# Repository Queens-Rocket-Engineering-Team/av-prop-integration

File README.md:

# Propulsion Integration Systems
> 2025-2026 Season - Propulsion Integration Projects

- Repository contains Avionics schematics, PCBs, and firmware for integrating with the propulsion stack.

### Folder Structure
- [`/Schematics`](./Schematics/) : Electrical design files (KiCad V8)  
- [`/Firmware`](./Firmware/) : C/C++ Code
- [`/Datasheets`](./Datasheets/) : Datasheets and reference materials  

### Documentation
- Boards and code are documented through `README` files in their respective directories. 

### Usage 
- To add or update features and work on new projects, create a new branch. 
- For **PCB** projects, name the branch with the convention: `pcb/board-name` or `pcb/board-feature` for updates.
- For **firmware** projects, name the branch with the convention: `fw/project-name` or `fw/project-feature` for updates.

--- 

QRET Avionics 25/26

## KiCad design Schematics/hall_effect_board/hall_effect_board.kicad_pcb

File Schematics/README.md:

# Propulsion Integration Schematics
This directory contains all schematics involved in this iteration of the Avionics Propulsion Integration system.
- All schematic and board files are created with **Kicad V8**.

Including: 

### Lower Control Board (Hydra)
- Launch control board for the **lower** valve bay. 
- Features valve control, analog sensing, and communication via CAN. 
- Interfaces with an STM32F103x8 microcontroller, controls two solenoids, reads from one Thermocouple, two Pressure Transducers, and two Hall-Effect sensors.

### Upper Control Board (Pegasus)
- Launch control board for the **upper** valve bay. 
- Features valve control, analog sensing, and communication via CAN **and** WIFI. 
- Interfaces with an ESP32-S3 microcontroller, controls two solenoids, reads two Pressure Transducers, and one Hall-Effect sensor.

### Hall Effect Breakout Board 
- Breakout board for a TMAG5273 Hall-Effect Sensor.
- Supports communication via I2C. 

### Shared Circuit Modules
- Circuitry used across both control boards.
- Solenoid control, pressure transducer and thermocouple entry circuitry. 

Usage:
> To create a new board
1. Launch KiCad v8. 
2. Navigate to the **File** menu and select **New Project...** or use the command `Ctrl+N`. 
3. This will open the file explorer. Ensure you are in the `/Schematics` directory. 
4. Name the new board descriptively -- this is also the name of the KiCad project.
    - A **descriptive** name clearly states its function or category. 
    - A name that follows the theme of the rocket should be kept on the board or in schematic files -- not as the name of the KiCad Project. (i.e. "Hydra" for the lower launch control board is a theme-following name)
    - Descriptive shorthands like `lc` (Launch Control) can be helpful in naming boards/projects.
5. Before creating the project, ensure the *Create a new folder for project* box is selected in the bottom-right section of the file explorer. 
6. Press "Save" to create a new project. 
7. In the folder created by KiCad, it wil be helpful to create folders for component symbols, footprints, and models. 
   - You're all done -- it's also always smart to look at existing projects for additional guidance.
  
> To add symbols, footprints, and models
1. Download and unzip resources from a provider like [SnapMagic](https://www.snapeda.com/home/) , [UltraLibrarian](https://www.ultralibrarian.com/), etc.
2. Move your downloaded resources.
    - For **symbols** move the raw `kicad_sym` file into your `symbols` folder.
    - For **footprints** move the `kicad_mod` file that is **in** an appropiately named folder into your `footprints` folder.
    - For **models** move the raw `STEP` file into your `models` folder.
3. To import resources navigate to the **Preferences** menu and select **Manage Symbol Libraries** -- note that this wil be **Manage Footprint Libraries** if you are in the PCB editor.
4. Switch the tab to **Project-Specific Libraries** and from there select the insert & folder icon to add your resource via the file explorer. 
5. After adding your resource select save and you're good to select it in the editor. 
   
6. For importing **3D-models**, navigate to the associated footprint in the PCB editor. 
7. Select it and press `E` to open the properties menu. 
8. Navigate to the **3D Models** tab to add your model through the file explorer. 
9. Press save. `Ctrl+S`

--- 

QRET Avionics 25/26

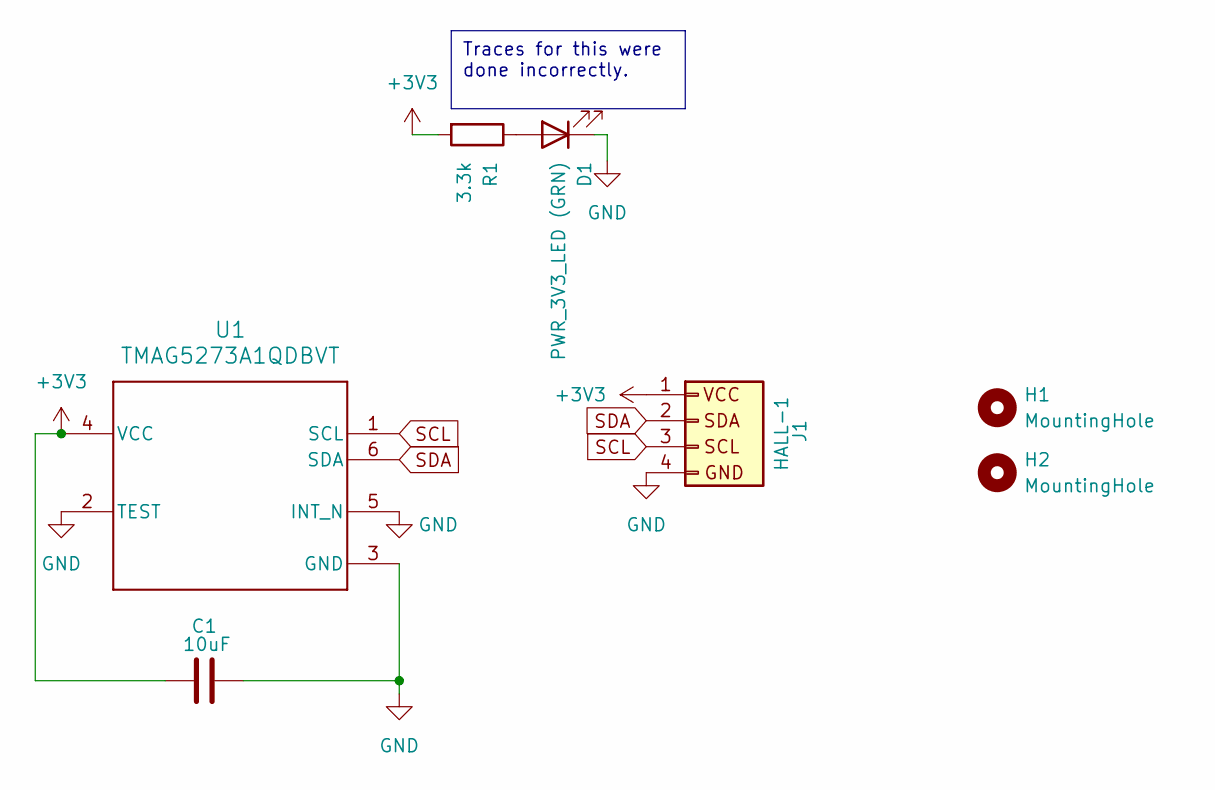
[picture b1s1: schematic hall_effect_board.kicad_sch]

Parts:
C1: 10uF; C_0805_2012Metric_Pad1.18x1.45mm_HandSolder; JLCSC C15850
D1: PWR_3V3_LED (GRN); LED_0603_1608Metric; JLCSC C2297
H1, H2: MountingHole; MountingHole_3.2mm_M3_ISO14580_Pad
J1: HALL-1; Molex_Nano-Fit_105313-xx04_1x04_P2.50mm_Horizontal; Digikey 455-S04B-PASK-2-ND
R1: 3.3k; R_0603_1608Metric; JLCSC C22978
U1: TMAG5273A1QDBVT; DBV0006A-IPC_A; Digikey 296-TMAG5273A1QDBVTCT-ND

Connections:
+3V3: C1.1, J1.1, R1.2, U1.4 (VCC)
GND: C1.2, D1.1 (K), J1.4, U1.2 (TEST), U1.3 (GND), U1.5 (INT_N)
unnamed: D1.2 (A), R1.1
SCL: J1.3, U1.1 (SCL)
SDA: J1.2, U1.6 (SDA)

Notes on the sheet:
Traces for this were done incorrectly.

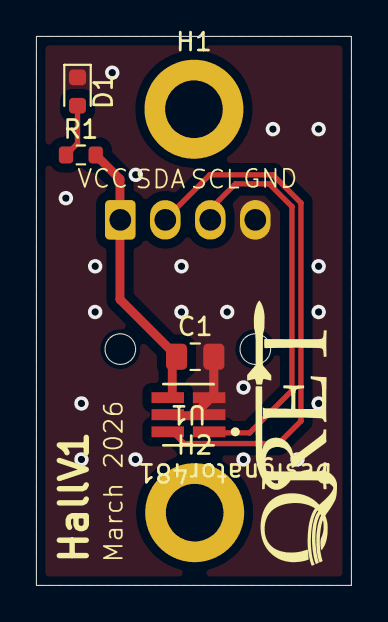
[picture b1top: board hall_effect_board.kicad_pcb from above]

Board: 2 copper layers, 17.5 x 30.5 mm, 7 parts (1 on the bottom side), 5 nets.

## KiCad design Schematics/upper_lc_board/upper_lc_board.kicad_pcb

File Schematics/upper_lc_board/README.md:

# Upper Control Board (PEGASUS) Documentation

<!--- removed left align div - weird github web issue --->
<details>
<summary><strong>Table of Contents</strong></summary>

- [Upper Control Board (PEGASUS) Documentation](#upper-control-board-pegasus-documentation)
  - [Overview](#overview)
    - [Key Features](#key-features)
  - [Circuit Design](#circuit-design)
    - [Power Management](#power-management)
      - [Power Entry](#power-entry)
      - [Power MUX](#power-mux)
      - [Power Switching](#power-switching)
    - [MCU Breakout](#mcu-breakout)
      - [Mode Selection](#mode-selection)
      - [CANBUS Interface](#canbus-interface)
      - [USB Interface](#usb-interface)
      - [System Feedback](#system-feedback)
    - [Valve Control](#valve-control)
    - [Sensing](#sensing)
      - [Data Acquisition](#data-acquisition)
      - [Pressure Transducers](#pressure-transducers)
  - [Board Design](#board-design)
    - [Physical Design Notes](#physical-design-notes)
    - [Electrical Characteristics](#electrical-characteristics)
    - [System Partitioning](#system-partitioning)
  - [Revision History](#revision-history)
  - [Contributors](#contributors)

</details>

---

## Overview

<em>Fig. 1: Pegasus</em>

The **Upper LC/Pegasus** board is a control board designed for integration with the rocket's propulsion system.
It operates in the **upper valve bay**, and drives a solenoid to control the rocket's vent valve.
This board supports analog pressure sensing, a digital hall-effect sensor for solenoid-status reading, and communication with the rest of the stack through CANbus. It is also **WiFi-capable**.

Interfaces with:
- ESP32-S3 Module
- Two 24V 205292 Solenoids
- Two 24V 4-20mA Pressure Transducers (PT)
- One TMAG273 digital hall-effect sensor (via breakout board)

### Key Features

- ESP32-S3 microcontroller with integrated WiFi
- I2C and SPI interfaces for sensor integration
- Controlled power delivery for sensors
- ORing circuits for power management
- Auditory and visual indication for status and debugging
- 4-layer PCB with dedicated ground planes
- Protection and filtering components across board

---

## Circuit Design

---

### Power Management

This board receives power from the Hybrid Power Module through the Backplane.
For more information on power delivery, check out [this repository](https://github.com/Queens-Rocket-Engineering-Team/av-power).

The supply delivers **three** levels of voltage to the board:

| Voltage (V) | Purpose |
|-------------|---------|
| 3.3 | Logic supply for microcontroller and other peripheral devices; also serves as a reference for signal conditioning and protection circuits |
| 5 | Intermediate supply for specific peripheral devices |
| 24 | High-voltage supply for driving external devices such as solenoids and sensors |

> **Note:** 3.3V is referred to as **3V3** throughout this document.

#### Power Entry

Power rails enter through a PCIe connector (Stack Edge Connector) and are conditioned by bulk filtering and input protection circuitry. These circuits apply to the 5V and 24V rails, each decoupled with 100 µF electrolytic capacitors to handle voltage transients and provide local energy storage. The 24V rail includes a 2A fuse for overcurrent protection.

Other power sources come from communication devices such as the USB connection, creating a voltage rail of 5V, which is then stepped down to 3V3 with a **Low-Dropout Regulator (LDO)**.

All rails feature test points and LEDs for diagnosis and debugging.

Additionally, the 24V rail uses a voltage divider for sensing. Two resistors (100 kΩ and 10 kΩ) scale the 24V input down to approx. 2.18V for measurement by an ESP32 ADC input:

$$V = 24 \times \frac{10k}{(100k + 10k)} \approx 2.18\ \text{V}$$

#### Power MUX

Power Multiplexers (MUX) are circuits that select between multiple power inputs to drive a single load. This is needed to avoid back-feeding between power sources, which could lead to unintended powering of interfaces and potential damage.

This implementation uses a **Dual OR-ing** circuit to select between two 3.3V inputs: Backplane (V_BP) and USB (V_USB).

- The circuit involves two Ideal Diode ICs, which use a MOSFET and controller to mimic the behaviour of an **Ideal Diode** (zero voltage drop when forward-biased, zero current when reverse-biased).
- The logic follows:
  - **ON condition**: A chip turns on if its V<sub>in</sub> is **higher** than the common output rail V<sub>out</sub>.
  - Each chip uses its enable *CE* pin to monitor the output rail -- if it sees a higher voltage present, it remains closed to prevent back-feeding.

In summary, a source will only drive the load if its voltage is higher than the current voltage on the output rail, allowing only **one** source to drive the output rail at a time.

- Capacitors are placed at the input pins to filter noise and prevent voltage spikes when a source is suddenly connected or disconnected.
- On the output rail, capacitors act as reservoirs to maintain steady voltage while also filtering noise generated by the loads connected to the 3V3 rail.

#### Power Switching

The delivery of 24V to the pressure transducers is controlled through a switching circuit.
- This was added to reduce power consumption by enabling sensor power only during active operation.
- The controlled output rail is identified as `VPT`.

The circuit uses a **CMOS** (dual-MOSFET) setup: one N-channel at the input to drive a P-channel for the output.

**MOSFET Basics**

| Type | ON Condition |
|------|-------------|
| N-Channel | Gate voltage higher than source -- V<sub>GS</sub> > V<sub>th</sub> |
| P-Channel | Gate voltage lower than source -- V<sub>GS</sub> < V<sub>th</sub> |

The **ON** state connects the **Drain** (output) pin to the **Source** pin.

**Logic**

- The ESP32 outputs a digital signal `VPT-SW` to drive the gate of the N-channel MOSFET. The source of the MOSFET is set to GND (0V).
- The gate is now at a higher voltage than the source, setting the drain to GND.
- The drain connects to a resistor divider with 24V to drive the gate of the P-channel MOSFET. The source of the MOSFET is set to 24V.
  - The resistor divider limits the gate voltage to approximately 14.81 V, lower than the source, setting the drain to 24V and powering the `VPT` rail.

$$V_g = 24 \times \frac{10k}{(6.2k + 10k)} \approx 14.81\ \text{V}$$

$$V_{gs} = 14.81 - 24 \approx -9.19\ \text{V}$$

> From the [DMP4065 Datasheet](${KIPRJMOD}/../../Datasheets/pMOSFET_DMP4065S-7_DS.pdf), V<sub>GS(max)</sub> = ±20 V -- within safe operating range.

- VPT is filtered with a Pi filter, featuring a ferrite bead between a 10 µF bulk capacitor and a 0.1 µF high-frequency decoupling capacitor to suppress both low-frequency ripple and high-frequency noise.

The circuit also includes two resistors at the MOSFET gate:
- **Series (Gate) Resistor**: Limits inrush current into the gate while controlling switching speed and protecting the MCU pin.
- **Pull-Down Resistor**: Connects signal to GND to define a default logic state when nothing is actively driving the gate.

---

### MCU Breakout

The [ESP32-S3](https://documentation.espressif.com/esp32-s3_datasheet_en.pdf) module was selected for this board's MCU.

Key features:
- Integrated 2.4 GHz WiFi
- Native USB Serial/JTAG controller
- Internal CAN controller (TWAI)
- Flexible GPIO matrix

#### Mode Selection

The S3 can be put into **BOOT** mode and **RESET** with onboard buttons.

**BOOT** mode determines whether the chip runs existing code from flash memory or waits to download new firmware.
- The ESP32 reads the state of the BOOT pin (IO0) during reset to select the appropriate boot mode.
- It is **active-low**: when pulled to GND, it will wait for new code over serial/USB.
- The circuit consists of a momentary push-button and a 0.1 µF capacitor to filter out button noise (debouncing).

**RESET** controls the Enable (EN) pin which is the ON/OFF (reset) switch for the ESP32.
- It is **active-low**: when pulled to GND it turns off the chip, and when released, it restarts.
- The circuit consists of a momentary push-button, a pull-up resistor to ensure the chip is enabled by default, and a 0.1 µF capacitor to filter out button noise (debouncing).

| BOOT0 Level | Boot Mode |
|-------------|-----------|
| HIGH | Programming Mode |
| LOW | Memory Mode |

#### CANBUS Interface

The S3 includes an internal CAN controller but requires a CAN transceiver to interface with the stack's CANBUS.
- Differential pairs from the backplane edge connector are routed to the CAN transceiver, which converts them into TX and RX signals for the S3.
- The CAN transceiver selected is a high-speed [TCAN1051](https://www.ti.com/lit/ds/symlink/tcan1051h.pdf).

#### USB Interface

The S3 includes an internal USB controller, eliminating any intermediate circuitry between the USB connector and S3.
- Differential pairs from the USB connector are routed directly to the S3.
- The S3 has an internal pull-up resistor on the positive USB data line.

#### System Feedback

This board incorporates visual and auditory feedback through LEDs and a buzzer.

- Visual indicators include WiFi status, CAN status, and a general DEBUG indicator.
  - These consist of standard current-driven LEDs and an ARGB LED.
- The buzzer provides general-purpose feedback when visual indication isn't available (in the stack).

---

### Valve Control

Valves are actuated via solenoids using MOSFET-based switching circuits driven by the MCU.
- The system uses a Festo 205292 solenoid to control the rocket vent valve.
  - Operates at 24V and is active-low.
  - Controlled via low-side switching (active when pulled to ground).
  - Interfaces through a MOLEX Nano-Fit connector.

The circuits consist of an N-channel MOSFET for low-side switching, flyback (Schottky) diodes for protection, and hardware-driven LEDs for visual indication.

> See the **MOSFET Basics** section under [Power Management](#power-management) for background on MOSFET operation.

**Logic**

- The solenoid positive terminal is connected to 24V.
- The STM32 outputs a digital signal that serves as the circuit's control input.
- This signal feeds an N-channel MOSFET with its source connected to GND (0V) and its drain connected to the negative terminal of the solenoid input (SOL_RET).
- The signal will turn the MOSFET `ON` since the gate voltage (3.3V) will be higher than the source voltage (0V).
- This connects the MOSFET drain to source, pulling the solenoid negative terminal to ground and actuating the valve.

**Protection & Filtering**

- A 40V, 3A SS34 Schottky diode is placed across the solenoid to provide a path for inductive flyback (voltage spike) current during turn-off.
  - This is common practice to protect against voltage spikes generated by inductive loads during switching.
- A local 0.1 µF capacitor is placed near the connector for high-frequency decoupling.

**Visual Indication**

- For indication and debugging a purely-hardware driven LED circuit was leveraged.
  - An LED with a series current-limiting resistor is placed across the solenoid, with the anode on the positive terminal and the cathode on the negative terminal.
  - By default, the anode is connected to 24V and the cathode is floating.
  - When the solenoid is driven and the negative terminal is pulled low, the LED is connected on both sides and emits.

---

### Sensing

This board interfaces with several external sensors, including analog pressure transducers and a digital hall-effect sensor.
- Pressure transducers are used for analog telemetry measurements.
- Hall-effect sensors are used for solenoid state detection and feedback.

#### Data Acquisition

Analog sensor data is acquired via an external **ADC** (Analog-to-Digital Converter) through the SPI protocol. Digital signals from hall-effect sensors are acquired through the I2C protocol.

The ADC used is the [ADS131M04](https://www.ti.com/lit/ds/symlink/ads131m04.pdf) -- 8 input channels, 24-bit resolution, 32 kSPS programmable sampling rate.
- Each input channel receives a voltage or differential voltage from a sensor (V<sub>ref</sub> = 1.2 V).
- A [delta-sigma](https://e2e.ti.com/blogs_/archives/b/precisionhub/posts/delta-sigma-adc-basics-understanding-the-delta-sigma-modulator) modulator converts the voltage into a high-frequency bitstream representing the input analog signal. This modulator is driven by an external crystal oscillator (8.319 MHz).
- The bitstream is then filtered to produce a clean, high-resolution digital value.
- The ADC sends a 24-bit number representing the measured voltage to the MCU via SPI.

An **RC filter** is used at the ADC inputs as a low-pass filter to smooth out high-frequency noise. The capacitor charges and discharges through the resistor, smoothing fast transients so the ADC sees a stable voltage.

> **Brief Overview on Analog Signals:** Analog signals vary continuously, taking any value within a given range, unlike digital signals which have discrete levels. Changes in a sensor's physical quantity are represented proportionally as a voltage or current signal.

#### Pressure Transducers

The PT circuits are built around signal conditioning and protection before the ADC.
- The PT used is a 4-20 mA [Setra 209H](https://www.setra.com/hubfs/Setra_Product_Data_Sheets/Model_209H_Spec_Sheet_2016_PRELIMINARY_WATERMARK.pdf) connected via Molex Nano-Fit.
- The signal line is initially referenced to GND through a 62 Ω shunt resistor to produce a voltage drop proportionate to the signal (current):

$$R_{shunt} = \frac{V_{ref}}{I_{max}} = \frac{1.2\ \text{V}}{0.02\ \text{A}} = 60\ \Omega$$

> A 62 Ω resistor was chosen for availability.

- The signal is then clamped to 3.3V and GND using low-leakage diodes.
- A 1 kΩ resistor is placed in series between the signal and diode to limit current into the diodes during overvoltage conditions, protecting the input from excessive current.
- The clamped signal then passes through a 200 Ω resistor connected to a 10 nF capacitor, forming the RC low-pass filter before being sampled by the ADC.

---

## Board Design

### Physical Design Notes

- The board measures 69.5 mm × 60 mm.
- Connectors are placed at the board edge for accessibility.

### Electrical Characteristics

The board is a 4-layer PCB with dedicated ground planes for noise reduction and signal integrity.

| Layer | Net | Purpose |
|-------|-----|---------|
| 1 | Signals + Power | Top-level routing |
| 2 | GND | Inner ground plane |
| 3 | GND | Inner ground plane |
| 4 | Signals + Power | Bottom-level routing |

- Inner ground planes minimize impedance in return paths and reduce EMI.
- Decoupling capacitors are placed close to IC power pins to reduce loop inductance.
- Valve control circuits use local ground pours to support high-current return paths (MOSFET source).
- The ESP32-S3 module requires a large local ground pour for stable grounding and RF performance.

### System Partitioning

- The board is partitioned into distinct analog, digital, and power domains to reduce noise coupling and improve signal integrity.
- Analog sensing circuitry is physically isolated from high-current valve control circuits.
- Power distribution is routed from the top of the board and propagates downward through regulated domains.
- High-current switching paths are separated from sensitive signal routing to minimize interference.

---

## Revision History

| Revision | Date | Description |
|----------|------|-------------|
| 0.0.1 | 2025-12-15 | Initial prototype with full peripheral integration |
| 0.0.2 | 2025-12-30 | Optimized routing and component placement |
| 1.1 | 2026-01-16 | Onboard trace cuts and adjustments to prevent short due to reversed diode in thermocouple circuitry |
| 2.0 | 2026-03-05 | Started prototype for second revision of board for manufacturing. Including fixed TC circuit, buzzer, and power control for PT supply |
| 2.1 | 2026-03-27 | Review sprint: route cleanup and silkscreen addition |

---

## Contributors

Jeevan Sanchez, Tristan Alderson

---

*QRET Avionics 25/26*

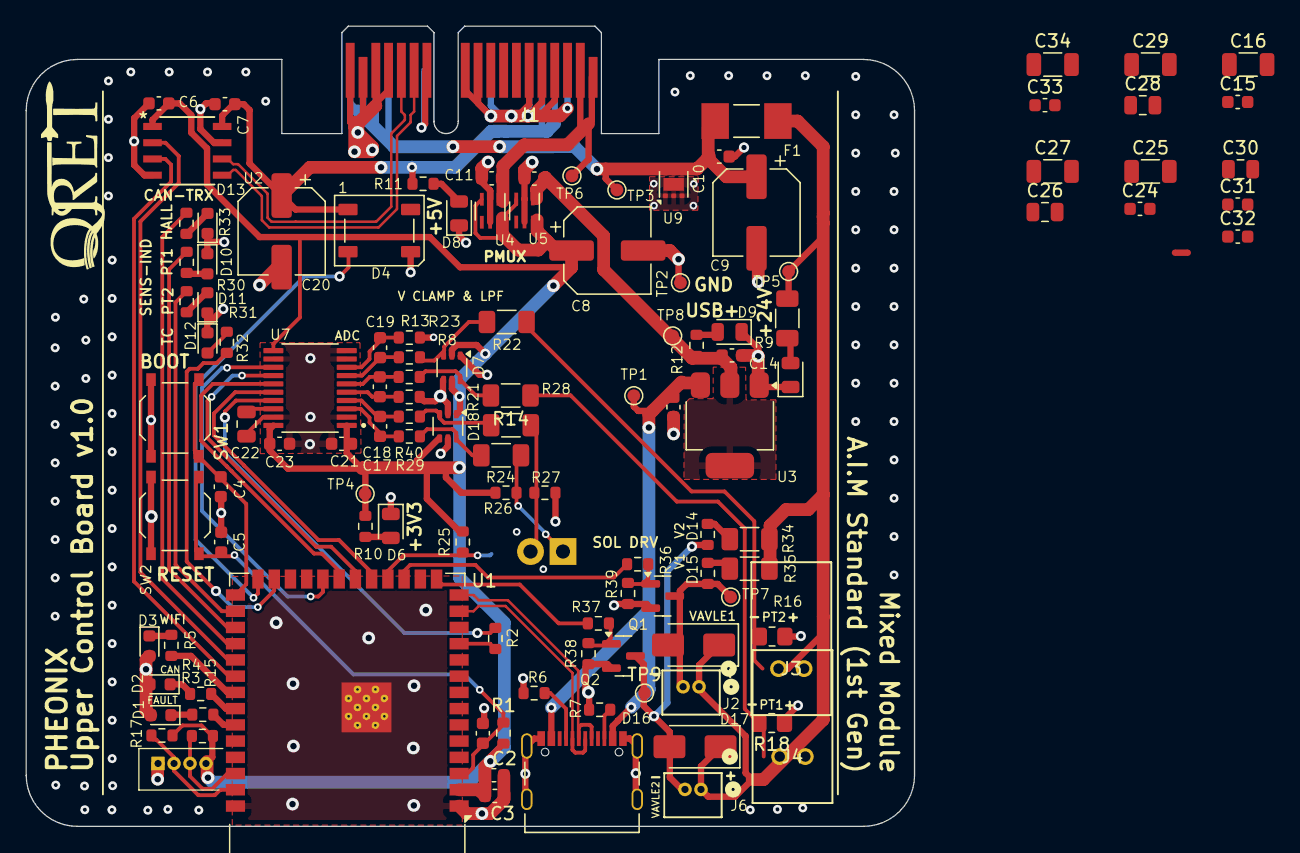
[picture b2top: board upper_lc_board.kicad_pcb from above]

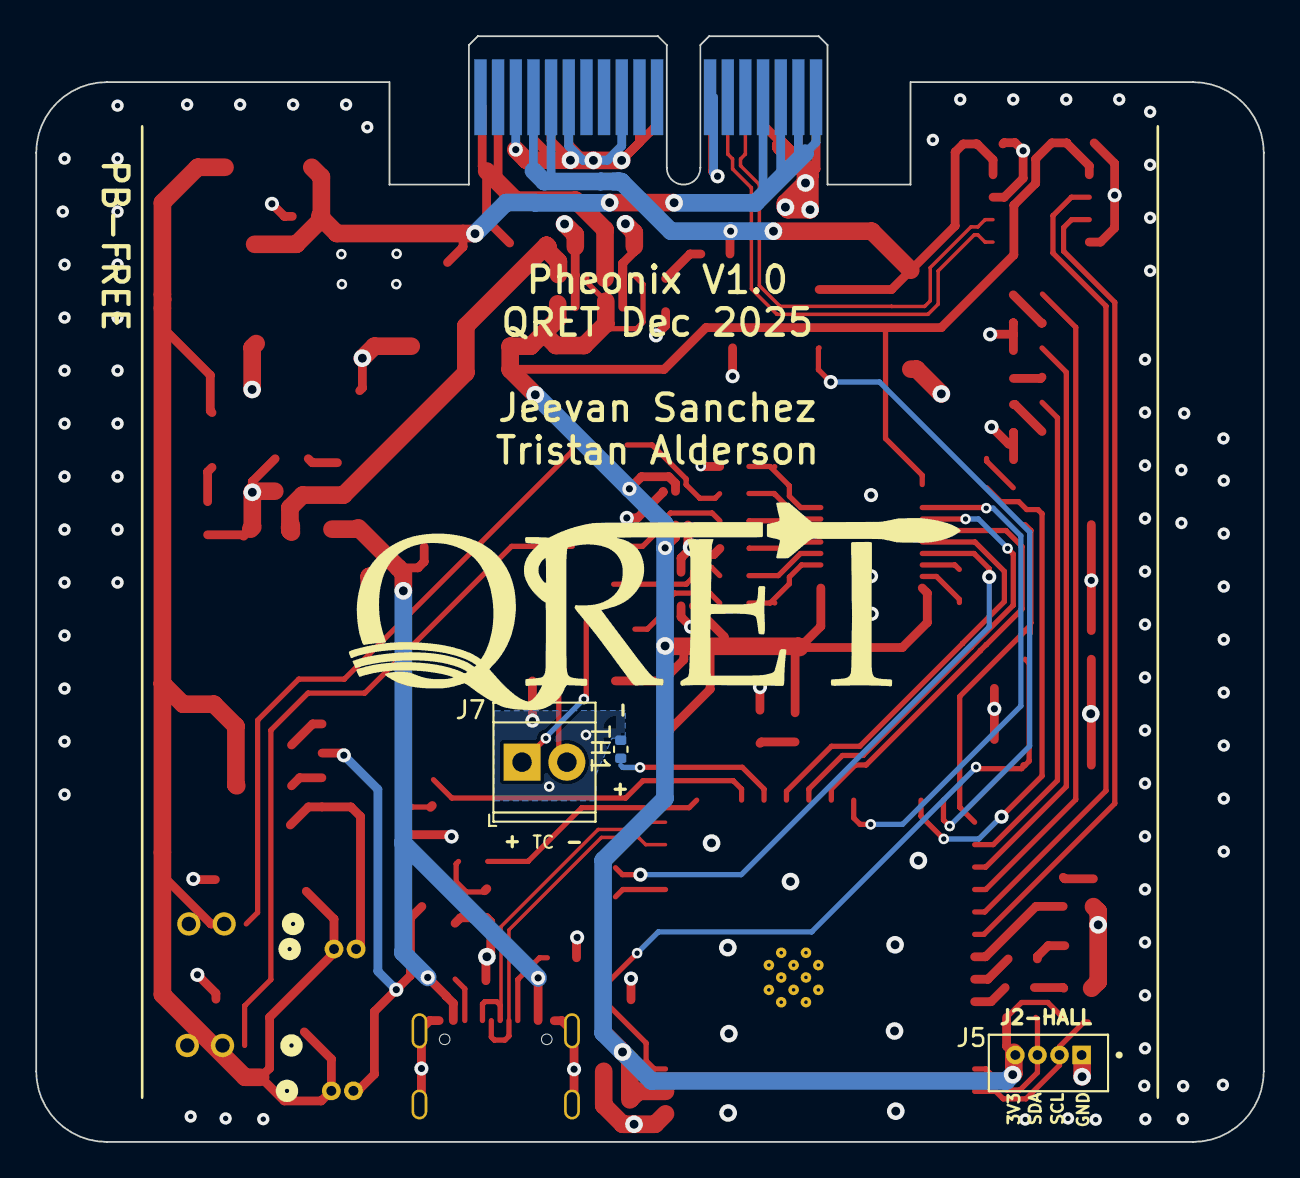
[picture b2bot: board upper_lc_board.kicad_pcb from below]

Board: 4 copper layers, 69.5 x 62.6 mm, 121 parts (3 on the bottom side), 73 nets.

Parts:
C1, C11, C12, C21, C23: 1uF; C_0603_1608Metric
C2, C4, C5, C6, C7, C10, C33: 0.1uF; C_0603_1608Metric
C3, C13, C14: 10uF; C_0603_1608Metric
C8, C9, C20: 100uF; CP_Elec_6.3x5.9
C15, C24: 0.1uF_50V; C_0603_1608Metric
C16, C25: 10uF_50V; C_1206_3216Metric
C17, C18, C19: 10nF; C_0603_1608Metric
C22: 220 nF; C_0805_2012Metric
C26, C28, C30: 0.1uF; C_0805_2012Metric
C27, C29: 10uF; C_1206_3216Metric
C31, C32: 1nF; C_0603_1608Metric
C34: 1uF_10V; C_1206_3216Metric
D1: FAULT_LED; LED_0603_1608Metric
D2: CAN_LED; LED_0603_1608Metric
D3: WIFI_LED; LED_0603_1608Metric
D4: SYS_LED_WS2812B; LED_WS2812B_PLCC4_5.0x5.0mm_P3.2mm
D5: PWR_24V_LED (GRN); LED_0805_2012Metric
D6: PWR_3V3_LED (GRN); LED_0805_2012Metric
D7, D18: BAV199DW; SOT-363_SC-70-6
D8: PWR_5V_LED (GRN); LED_0805_2012Metric
D9: USB_LED (GRN); LED_0805_2012Metric
D10, D11, D12, D13: LED; LED_0603_1608Metric
D14: SOL2_LED (YELW); R_0603_1608Metric
D15: SOL1_LED (YELW); R_0603_1608Metric
D16, D17: SS34; D_SMA
F1: Fuse; FUSC6125X279N
J1: Stack Male Edge Connector; BUS_PCIexpress_x1
J2, J6: SOL_CONN; CONN02_530470260_MOL
J3, J4: PT1; CONN2_S02B-PASK-2_JST
J5: HALL; MOLEX_53047-0460
J7: Screw_Terminal_01x02; TerminalBlock_TE_282834-2_1x02_P2.54mm_Horizontal
J8: USB_C_Female_USB2_Small; USB_C_DB-108PWB
NT1: GND-TIE; NetTie-2_SMD_Pad0.5mm
Q1, Q2: AO3400A; SOT-23
R1, R25: 10k; R_0603_1608Metric
R2: 33; R_0603_1608Metric
R3, R4, R5, R10, R12, R30, R31, R32, R33: 150; R_0603_1608Metric
R6, R7: 5.1k; R_0603_1608Metric
R8, R13, R29, R36, R37, R40: 200; R_0603_1608Metric
R9, R34, R35: 4.7k; R_1206_3216Metric_Pad1.30x1.75mm_HandSolder
R11: 510; R_0603_1608Metric
R14, R22, R24, R28: 1k; R_1206_3216Metric_Pad1.30x1.75mm_HandSolder
R15, R17: 2.2k; R_0603_1608Metric
R16, R18: 165; R_0805_2012Metric_Pad1.20x1.40mm_HandSolder
R21, R23: 1.2k; R_0603_1608Metric
R26, R27: 1M; R_0603_1608Metric
R38, R39: 100k; R_0603_1608Metric
SW1: SW_ESP_BOOT_MODE; SW_Push_1P1T_XKB_TS-1187A
SW2: SW_ESP_RESET; SW_Push_1P1T_XKB_TS-1187A
TH1: Thermistor; R_0402_1005Metric
TP1: 5V_USB; TestPoint_Pad_D1.0mm
TP2: GND; TestPoint_Pad_D1.0mm
TP3: 24V_BP; TestPoint_Pad_D1.0mm
TP4: 3V3; TestPoint_Pad_D1.0mm
TP5: 24V; TestPoint_Pad_D1.0mm
TP6: 3V3_BP; TestPoint_Pad_D1.0mm
TP7: VALVE1_OUT_TP; TestPoint_Pad_D1.0mm
TP8: 3V3_USB; TestPoint_Pad_D1.0mm
TP9: VALVE2_OUT_TP; TestPoint_Pad_D1.0mm
U1: ESP32-S3-WROOM-1-N16; ESP32-S3-WROOM-1
U2: ISO1044BDR; SOIC_1044BDR_TEX
U3: AMS1117; SOT-223-3_TabPin2
U4, U5: ID_LM66100DCKR; SC-70-6
U7: ADC_ADS131M04IPWR; SOP65P640X120-20N
U9: TVS3300DRV; WSON-6-1EP_2x2mm_P0.65mm_EP1x1.6mm

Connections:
5V_USB: C13.1, J8.A4 (VBUS), J8.A9 (VBUS), J8.B4 (VBUS), J8.B9 (VBUS), TP1.1, U3.3 (VI)
+3V3: C2.1, C3.1, C6.1, C8.1, C21.2, C23.2, C33.1, C34.1, D7.2 (K2), D7.5 (K4), D18.2 (K2), D18.5 (K4), J5.4, R1.1, R10.2, R15.2, R17.1, R25.2, R26.1, TP4.1, U1.2 (3V3), U2.1 (VCC1), U4.3 (*CE), U4.6 (VOUT), U5.3 (*CE), U5.6 (VOUT), U7.1 (AVDD), U7.11 (~SYNC/~RESET), U7.20 (DVDD)
+5V: C7.1, C20.1, D4.1 (VDD), J1.A4 (5.0V_A), J1.A5 (5.0V_A), R11.2, U2.8 (VCC2)
+24V: C15.1, C16.1, C24.1, C25.1, D16.1 (K), D17.1 (K), F1.1, J2.1, J6.1, R9.2, R34.2, R35.2, TP5.1
+24V_BP: C10.1, J1.A15 (24V_C), J1.A16 (24V_C), J1.A17 (24V_C), J1.A18 (24V_C), TP3.1, U9.4 (IN), U9.5 (IN), U9.6 (IN)
/ESP Breakout Cirucitry/ESP32_EN: C1.1, C5.2, R1.2, SW2.2, U1.3 (EN)
/ESP Breakout Cirucitry/ESP32_IO0: C4.2, SW1.2, U1.27 (IO0)
/ESP Breakout Cirucitry/GPIO_18: R2.1, U1.11 (IO18)
/ESP Breakout Cirucitry/GPIO_38: U1.31 (IO38), U2.2 (TXD)
/ESP Breakout Cirucitry/GPIO_39: U1.32 (IO39), U2.3 (RXD)
/ESP Breakout Cirucitry/GPIO_40: R5.1, U1.33 (IO40)
/ESP Breakout Cirucitry/GPIO_41: R4.1, U1.34 (IO41)
/ESP Breakout Cirucitry/GPIO_42: R3.1, U1.35 (IO42)
/ESP Breakout Cirucitry/GPIO_45: D4.2 (DOUT), U1.26 (IO45)
/ESP Breakout Cirucitry/USB_N: J8.A7 (D-), J8.B7 (D-), U1.13 (USB_D-)
/ESP Breakout Cirucitry/USB_P: J8.A6 (D+), J8.B6 (D+), U1.14 (USB_D+)
/Power Circuitry/3V3_BP: C11.2, J1.A1 (3.3V_A), J1.A2 (3.3V_A), TP6.1, U4.1 (VIN)
/Power Circuitry/3V3_USB: C12.1, C14.1, R12.1, TP8.1, U3.2 (VO), U5.1 (VIN)
/Sensor Circuitry/PT1: J4.2, R14.1, R18.2
/Sensor Circuitry/PT1_CLAMPED: C18.2, R13.1, U7.6 (AIN1P)
/Sensor Circuitry/PT2: J3.2, R16.2, R22.1
/Sensor Circuitry/PT2_CLAMPED: C19.2, R8.1, U7.7 (AIN2P)
/Sensor Circuitry/PT-1/VIN: C26.1, C27.1, J4.1
/Sensor Circuitry/PT-2/VIN: C28.1, C29.1, J3.1
/Sensor Circuitry/TC_N: C30.1, C32.2, J7.2, R27.1, R28.2
/Sensor Circuitry/TC_N_CLAMPED: C17.1, R40.2, U7.4 (AIN0N)
/Sensor Circuitry/TC_P: C30.2, C31.2, J7.1, R24.2, R26.2
/Sensor Circuitry/TC_P_CLAMPED: C17.2, R29.2, U7.3 (AIN0P)
ADC_CLKIN: R2.2, U7.17 (CLKIN)
ADC_DREADY: U1.22 (IO14), U7.13 (~DRDY)
ADC_MISO: U1.21 (IO13), U7.15 (DOUT)
ADC_MOSI: U1.19 (IO11), U7.16 (DIN)
ADC_SCLK: U1.20 (IO12), U7.14 (SCLK)
CAN_+: J1.B14 (CAN_H), U2.6 (CANH)
CAN_-: J1.B13 (CAN_L), U2.5 (CANL)
GND: C1.2, C2.2, C3.2, C4.1, C5.1, C6.2, C7.2, C8.2, C9.2, C10.2, C11.1, C12.2, C13.2, C14.2, C15.2, C16.2, C20.2, C23.1, C24.2, C25.2, C33.2, C34.2, D1.2 (A), D2.2 (A), D3.2 (A), D4.3 (VSS), D5.1 (K), D6.1 (K), D8.1 (K), D9.1 (K), D10.1 (K), D11.1 (K), D12.1 (K), D13.1 (K), J1.A3 (GND_A), J1.A6 (GND_A), J1.A9 (GND_B), J1.A12 (GND_B), J1.B4 (GND_A), J1.B5 (GND_A), J1.B6 (GND_A), J1.B10 (GND_B), J1.B11 (GND_B), J1.B12 (GND_B), J1.B15 (GND_C), J1.B16 (GND_C), J1.B17 (GND_C), J1.B18 (GND_C), J5.1, J8.A1 (GND), J8.A12 (GND), J8.B1 (GND), J8.B12 (GND), J8.S1 (SHIELD), NT1.2, Q1.2 (S), Q2.2 (S), R6.2, R7.2, R38.1, R39.1, SW1.1, SW2.1, TP2.1, U1.1 (GND), U1.40 (GND), U1.41 (GND), U2.4 (GND1), U2.7 (GND2), U3.1 (ADJ), U4.2 (GND), U4.5 (ST), U5.2 (GND), U5.5 (ST), U7.12 (~CS), U7.19 (DGND), U9.1 (GND), U9.2 (GND), U9.3 (GND), U9.7 (GND)
GNDA: C21.1, C22.2, C26.2, C27.2, C28.2, C29.2, C31.1, C32.1, D7.1 (A1), D7.4 (A3), D18.1 (A1), D18.4 (A3), NT1.1, R16.1, R18.1, R21.1, R23.1, R27.2, TH1.2, U7.2 (AGND), U7.9 (AIN3N), U7.10 (AIN3P)
HALL_LED: R33.1, U1.30 (IO37)
HALL_SCL: J5.2, R17.2, U1.39 (IO1)
HALL_SDA: J5.3, R15.1, U1.38 (IO2)
unnamed: C9.1, F1.2
unnamed: D1.1 (K), R3.2
unnamed: D2.1 (K), R4.2
unnamed: D3.1 (K), R5.2
unnamed: D5.2 (A), R9.1
unnamed: D6.2 (A), R10.1
unnamed: D7.6 (K3A4), R13.2, R14.2
unnamed: D7.3 (K1A2), R8.2, R22.2
unnamed: D8.2 (A), R11.1
unnamed: D9.2 (A), R12.2
unnamed: D10.2 (A), R30.2
unnamed: D11.2 (A), R31.2
unnamed: D12.2 (A), R32.2
unnamed: D13.2 (A), R33.2
unnamed: D14.2 (A), R34.1
unnamed: D15.2 (A), R35.1
unnamed: D18.6 (K3A4), R24.1, R29.1
unnamed: D18.3 (K1A2), R28.1, R40.1
unnamed: J8.A5 (CC1), R6.1
unnamed: J8.B5 (CC2), R7.1
unnamed: Q1.1 (G), R36.1, R39.2
unnamed: Q2.1 (G), R37.1, R38.2
unnamed: C18.1, R21.2, U7.5 (AIN1N)
unnamed: C19.1, R23.2, U7.8 (AIN2N)
unnamed: C22.1, U7.18 (CAP)
PT1_LED: R30.1, U1.29 (IO36)
PT2_LED: R31.1, U1.28 (IO35)
SOL1_RET: D15.1 (K), D16.2 (A), J2.2, Q1.3 (D)
SOL2_RET: D14.1 (K), D17.2 (A), J6.2, Q2.3 (D)
TC_LED: R32.1, U1.25 (IO48)
TEMP_SENSE: R25.1, TH1.1, U1.18 (IO10)
VALVE1_CTRL: R36.2, U1.17 (IO9)
VALVE2_CTRL: R37.2, U1.15 (IO3)

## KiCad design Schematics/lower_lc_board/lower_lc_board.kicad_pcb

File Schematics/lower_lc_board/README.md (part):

# Lower Control Board (HYDRA) Documentation

<!--- removed left align div - weird github web issue --->
<details>
<summary><strong>Table of Contents</strong></summary>
  
  - [Overview](#overview)
    - [Key Features](#key-features)
  - [Circuit Design](#circuit-design)
    - [Power Management](#power-management)
      - [Power Entry](#power-entry)
      - [Power MUX](#power-mux)
      - [Power Switching](#power-switching)
    - [MCU Breakout](#mcu-breakout)
      - [Mode Selection](#mode-selection)
      - [Flash Storage Module](#flash-storage-module)
      - [CANBUS Interface](#canbus-interface)
      - [Serial Wire Debug](#serial-wire-debug)
      - [USB Interface](#usb-interface)
      - [System Feedback](#system-feedback)
    - [Valve Control](#valve-control)
    - [Sensing](#sensing)
      - [Data Acquisition](#data-acquisition)
      - [Pressure Transducers](#pressure-transducers)
      - [Thermocouples](#thermocouples)
  - [Board Design](#board-design)
    - [Physical Design Notes](#physical-design-notes)
    - [Electrical Characteristics](#electrical-characteristics)
    - [System Partitioning](#system-partitioning)
  - [Revision History](#revision-history)
  - [Contributors](#contributors)

</details>

---

## Overview

<em>Fig. 1: 3D-rendered view of the lower control board.</em>

The **Lower LC/Hydra** board is a control board designed for integration with the rocket's propulsion system.
It operates in the **lower valve bay**, and drives solenoids to control the **dump** and **fill** valves.
This board supports analog pressure and temperature sensing, two digital hall-effect sensors for solenoid-status reading, and communication with the rest of the stack through CANbus.

Interfaces with:
- STM32F1 MCU
- Two 24V 205292 Solenoids
- Two 24V 4-20mA Pressure Transducers (PT)
- An Omega SA3-K Thermocouple (TC)
- Two TMAG273 digital hall-effect sensors (via breakout board)

### Key Features

- STM32F1 microcontroller with additional memory
- I2C and SPI interfaces for sensor integration
- Controlled power delivery for sensors and solenoids
- ORing circuits for power management
- Visual indication for status and debugging
- 4-layer PCB with dedicated ground planes
- Protection and filtering components across board

---

## Circuit Design

This board is primarily composed of four circuit modules representing its critical systems: [Power Management](#power-management), [STM32 Breakout](#mcu-breakout), [Valve Control](#valve-control), and [Sensing](#sensing).

All schematics are available as `kicad_sch` files in this directory.

---

### Power Management

This board receives power from the Hybrid Power Module through the Backplane.
For more information on power delivery, check out [this repository](https://github.com/Queens-Rocket-Engineering-Team/av-power).

The supply delivers **three** levels of voltage to the board:

| Voltage (V) | Purpose |
|-------------|---------|
| 3.3 | Logic supply for microcontroller and other peripheral devices; also serves as a reference for signal conditioning and protection circuits |
| 5 | Intermediate supply for specific peripheral devices |
| 24 | High-voltage supply for driving external devices such as solenoids and sensors |

> **Note:** 3.3V is referred to as **3V3** throughout this document.

#### Power Entry

Power rails enter through a Molex Micro-Fit connector and are conditioned by bulk filtering and input protection circuitry. These circuits apply to the 5V and 24V rails, each decoupled with 100 µF electrolytic capacitors to handle voltage transients and provide local energy storage. The 24V rail includes a 2A fuse for overcurrent protection.

Other power sources come from communication devices such as the USB connection and the JTAG debugger. The USB creates a voltage rail of 5V, which is then stepped down to 3V3 with a **Low-Dropout Regulator (LDO)**. The JTAG debugger supplies 3V3.

All rails feature test points and LEDs for diagnosis and debugging.

#### Power MUX

Power Multiplexers (MUX) are circuits that select between multiple power inputs to drive a single load. This is needed to avoid back-feeding between power sources, which could lead to unintended powering of interfaces and potential damage.

This implementation uses a **Triple OR-ing** circuit to select between three 3.3V inputs: Backplane (V_BP), JTAG (V_SWD), and USB (V_USB).

- The circuit involves three Ideal Diode ICs, which use a MOSFET and controller to mimic the behaviour of an **Ideal Diode** (zero voltage drop when forward-biased, zero current when reverse-biased).
- The logic follows:
  - **ON condition**: A chip turns on if its *Vin* is **higher** than the common output rail *Vout*.
  - Each chip uses its enable *CE* pin to monitor the output rail; if it sees a higher voltage present, it remains closed to prevent back-feeding.

In summary, a source will only drive the load if its voltage is higher than the current voltage on the output rail, allowing only **one** source to drive the output rail at a time.

- Capacitors are placed at the input pins to filter noise and prevent voltage spikes when a source is suddenly connected or disconnected.
- On the output rail, capacitors act as reservoirs to maintain steady voltage while also filtering noise generated by the loads connected to the 3V3 rail.

#### Power Switching

The delivery of 24V to the pressure transducers and solenoids is controlled through a switching circuit.

- For PTs, this was added to reduce power consumption by enabling sensor power only during active operation.
- For solenoids, this was added as a pre-actuation layer to provide additional protection and controlled switching.
- The controlled output rails are identified as `VPT` and `VSOL` respectively.

The circuit uses a **CMOS** (dual-MOSFET) setup: one N-channel at the input to drive a P-channel for the output.

**MOSFET Basics**

| Type | ON Condition |
|------|-------------|
| N-Channel | Gate voltage higher than source -> V<sub>GS</sub> > V<sub>th</sub> |
| P-Channel | Gate voltage lower than source -> V<sub>GS</sub> < V<sub>th</sub> |

The **ON** state connects the **Drain** (output) pin to the **Source** pin.

**Logic**

- The STM32 outputs a digital signal to drive the gate of the N-channel MOSFET. The source of the MOSFET is set to GND (0V).
- The gate is now at a higher voltage than the source, setting the drain to GND.
- The drain connects to a resistor divider with 24V to drive the gate of the P-channel MOSFET. The source of the MOSFET is set to 24V.
  - The resistor divider limits the gate voltage to approximately 14.81 V, lower than the source, setting the drain to 24V and powering the output rail.

$$V_g = 24 \times \frac{10k}{(6.2k + 10k)} \approx 14.81\ \text{V}$$

$$V_{gs} = 14.81 - 24 \approx -9.19\ \text{V}$$

> From the [DMP4065 Datasheet](${KIPRJMOD}/../../Datasheets/pMOSFET_DMP4065S-7_DS.pdf), V<sub>GS(max)</sub> = ±20 V, within safe operating range.

- `VPT` is filtered using a Pi filter with a ferrite bead between a 10 µF bulk capacitor and a 0.1 µF decoupling capacitor to reduce ripple and high-frequency noise.
- `VSOL` is decoupled with a 100 µF electrolytic capacitor for local energy storage and transient support.
- `VSOL` also uses a voltage divider for sensing. Two resistors (100 kΩ and 10 kΩ) scale the 24V input down to approx. 2.18V for measurement by an STM32 ADC input:

$$V = 24 \times \frac{10k}{(100k + 10k)} \approx 2.18\ \text{V}$$

The circuit also includes two resistors at the MOSFET gate:
- **Series (Gate) Resistor**: Limits inrush current into the gate while controlling switching speed and protecting the MCU pin.
- **Pull-Down Resistor**: Connects signal to GND to define a default logic state when nothing is actively driving the gate.

---

### MCU Breakout

The [STM32F103](https://www.st.com/resource/en/datasheet/stm32f103cb.pdf) was selected for this board's MCU.

Key features:
- 72 MHz ARM Cortex-M3 core
- Internal CAN controller
- Compact LQFP48 package

#### Mode Selection

The STM32 can be put into **BOOT** mode and **RESET** with onboard buttons.

**BOOT** mode determines whether the chip runs existing code from flash memory or waits to download new firmware.
- The STM32 reads the state of the BOOT pin (BOOT0) during reset to select the appropriate boot mode.
- It is **active-high**: when pulled HIGH (3V3), it will wait for new code over serial/USB.
- The circuit consists of a momentary push-button and a pull-down resistor to ensure the chip is disabled by default. A second BOOT pin (BOOT1) is pulled low to prevent entering SRAM mode.

**RESET** controls the Reset (NRST) pin --- the ON/OFF switch for the STM32.
- It is **active-low**: when pulled to GND the chip turns off; when released, it restarts.
- The circuit consists of a momentary push-button, a pull-up resistor to ensure the chip is enabled by default, and a 0.1 µF capacitor to filter out button noise (debouncing).

| BOOT0 Level | Boot Mode |
|-------------|-----------|
| HIGH | Programming Mode |
| LOW | Memory Mode |

#### Flash Storage Module

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
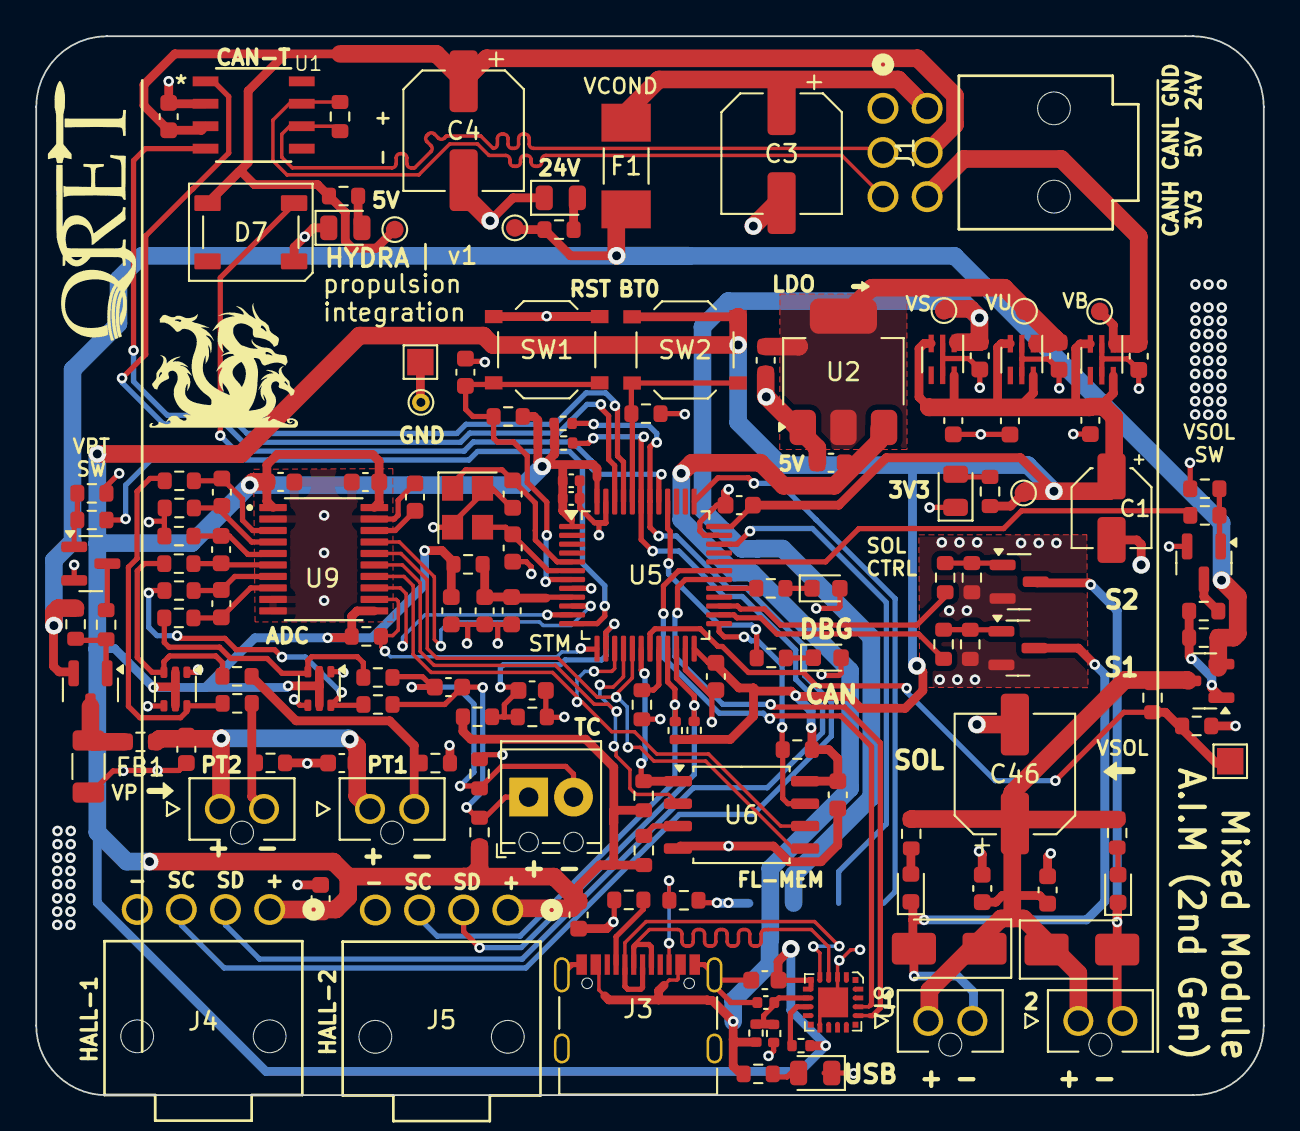
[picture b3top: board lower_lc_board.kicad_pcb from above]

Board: 4 copper layers, 69.5 x 60.0 mm, 149 parts (1 on the bottom side), 87 nets.

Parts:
C1: 10uF; CP_Elec_4x5.4
C2, C18, C23, C30, C33, C39, C41, C45, C52: 0.1uF; C_0603_1608Metric
C3, C4, C46: 100uF; CP_Elec_6.3x5.9
C5, C6, C28, C43, C44, C48, C49: 1uF; C_0603_1608Metric
C7, C12, C21, C50: 10uF; C_0603_1608Metric
C8, C9, C17: 100nF; C_0603_1608Metric
C10, C11: 10p; C_0603_1608Metric
C13, C14: 100n; C_0402_1005Metric
C15, C16: 100n; C_0603_1608Metric
C20: 1uF; C_0402_1005Metric
C26, C27, C34, C56: 10nF; C_0603_1608Metric
C29: 220 nF; C_0603_1608Metric
C35: 10uF; C_1206_3216Metric
C51: 1nF; C_0603_1608Metric
D1: PWR_3V3_LED (GRN); LED_0805_2012Metric
D2: PWR_24V_LED (GRN); LED_0805_2012Metric
D3: PWR_5V_LED (GRN); LED_0805_2012Metric
D4: USB_LED (GRN); LED_0805_2012Metric
D5: DB_LED (YLW); LED_0603_1608Metric
D6: CAN_LED (WHT); LED_0603_1608Metric
D7: SYS_LED; LED_WS2812B_PLCC4_5.0x5.0mm_P3.2mm
D11: SOL2_LED (YELW); LED_0603_1608Metric
D12: SOL1_LED (YELW); LED_0603_1608Metric
D13, D18: BAV199DW; SOT-363_SC-70-6
D15, D16: SS34; D_SMA
F1: Fuse; FUSC6125X279N
FB1, FB2: 600R; R_0603_1608Metric
J1: Conn_01x06; CONN_SD-105314-100_06_MOL
J2: SWD_CONN; SWD_PinHeader_1x04_P2.54mm_Horizontal_SMD
J3: USB_C_CONN; USB_C_DB-108PWB
J4: HALL-1; CONN_SD-105313-100_04_MOL
J5: HALL-2; CONN_SD-105313-100_04_MOL
J6, J8: PT; MOLEX_1053091102
J7: Screw_Terminal_01x02; TerminalBlock_Phoenix_MPT-0,5-2-2.54_1x02_P2.54mm_Horizontal
J9, J10: SOL_CONN; MOLEX_1053091102
Q1, Q2: AO3400A; SOT-23
Q3, Q5: 2N7002; SOT-23
R1: 3.3k; R_0603_1608Metric
R2, R30, R31: 12k; R_0603_1608Metric
R3, R16, R23, R51: 6.2k; R_0603_1608Metric
R5, R6, R7, R8, R22, R25, R43, R48, R49, R50, R52, R54, R60: 10k; R_0603_1608Metric
R9, R10: 5.1k; R_0603_1608Metric
R11: 22k; R_0402_1005Metric
R12: 47k; R_0402_1005Metric
R13: 1k; R_0402_1005Metric
R14: 680; R_0603_1608Metric
R15: 270; R_0603_1608Metric
R17, R18, R21, R45: 2.2k; R_0402_1005Metric
R19, R20: 1.2k; R_0603_1608Metric
R24, R28, R33, R37: 1k; R_0603_1608Metric
R26, R27: 1M; R_0603_1608Metric
R29, R34, R36, R38, R40, R41, R44, R53: 200; R_0603_1608Metric
R32, R35: 62; R_0603_1608Metric
R39, R42, R47: 100k; R_0603_1608Metric
R46: 120; R_0603_1608Metric
SW1: SW_STM_RESET; SW_Push_1P1T_XKB_TS-1187A
SW2: SW_STM_BOOT_MODE; SW_Push_1P1T_XKB_TS-1187A
TH1: Thermistor; R_0603_1608Metric
TP1: 24V-TP; TestPoint_Pad_D1.0mm
TP2: 3V3-TP; TestPoint_Pad_D1.0mm
TP3: GND-TP-H; TestPoint_THTPad_D1.0mm_Drill0.5mm
TP4: 3V3_BP; TestPoint_Pad_D1.0mm
TP5: GND-TP-P; TestPoint_Pad_1.5x1.5mm
TP6: 3V3_USB; TestPoint_Pad_D1.0mm
TP7: VSOL.S; TestPoint_Pad_1.5x1.5mm
TP9: V_SWD_TP; TestPoint_Pad_D1.0mm
TP13: 5V-TP; TestPoint_Pad_D1.0mm
U1: TCAN1051HGVDR; SOIC_1044BDR_TEX
U2: AMS1117-3.3; SOT-223-3_TabPin2
U3, U4, U10: ID_LM66100DCKR; SC-70-6
U5: STM32F103CBT6; LQFP-48_7x7mm_P0.5mm
U6: BY25Q128ES; SOIC-8_5.23x5.23mm_P1.27mm
U8: CP2102N-Axx-xQFN20; QFN-20-1EP_3x3mm
U9: ADC_ADS131M04IPWR; SOP65P640X120-20N
U11, U12: DMP4065S-7; SOT-23
Y1: X322516MMB4SI; Crystal_SMD_3225-4Pin_3.2x2.5mm

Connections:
5V_USB: C7.1, J3.A4 (VBUS), J3.A9 (VBUS), J3.B4 (VBUS), J3.B9 (VBUS), R11.2, R16.1, U2.3 (VI)
+3.3VA: C45.2, C48.2, FB2.1, U5.9 (VDDA)
+3V3: C1.1, C13.1, C14.1, C15.1, C16.1, C17.1, C21.2, C23.1, C28.2, C33.1, C43.2, C49.1, C50.1, C51.1, C52.1, D13.2 (K2), D13.5 (K4), D18.2 (K2), D18.5 (K4), FB2.2, J4.1, J5.1, R1.1, R6.2, R7.2, R8.2, R13.2, R17.2, R18.1, R21.2, R25.2, R26.1, R45.1, R48.1, R49.2, SW2.2, TP2.1, U3.3 (*CE), U3.6 (VOUT), U4.3 (*CE), U4.6 (VOUT), U5.1 (VBAT), U5.24 (VDD), U5.36 (VDD), U5.48 (VDD), U6.8 (VCC), U8.6 (VDD), U8.7 (VREGIN), U9.1 (AVDD), U9.11 (~SYNC/~RESET), U9.20 (DVDD), U10.3 (*CE), U10.6 (VOUT)
+5V: C4.1, C9.2, D7.1 (VDD), J1.5, R3.2, TP13.1, U1.3 (VCC)
+24V: F1.1, R2.2, R23.2, R51.2, TP1.1, U11.2 (S), U12.2 (S)
+24V_BP: C3.1, F1.2, J1.4
/Power Circuitry/3V3_BP: C5.2, J1.6, TP4.1, U3.1 (VIN)
/Power Circuitry/3V3_USB: C6.1, C12.1, TP6.1, U2.2 (VO), U4.1 (VIN)
/Sensing Circuitry/PT1_CLAMPED: C26.2, R34.1, U9.3 (AIN0P)
/Sensing Circuitry/PT2_CLAMPED: C27.2, R38.1, U9.6 (AIN1P)
/Sensing Circuitry/TC_N_1: C30.1, J7.2, R27.1, R28.2
/Sensing Circuitry/TC_N_CLAMPED_1: C56.1, R40.2, U9.8 (AIN2N)
/Sensing Circuitry/TC_P_1: C30.2, J7.1, R24.2, R26.2
/Sensing Circuitry/TC_P_CLAMPED_1: C56.2, R29.2, U9.7 (AIN2P)
/Valve Control Circuitry/VSOL: C39.1, C41.1, C46.1, D15.1 (K), D16.1 (K), J9.1, J10.1, R30.2, R31.2, R47.1, U12.3 (D)
ADC_CLKIN: U5.10 (PA0), U9.17 (CLKIN)
ADC_CS: R49.1, U5.13 (PA3), U9.12 (~CS)
ADC_DRDY: U5.11 (PA1), U9.13 (~DRDY)
BOOT0: R5.2, SW2.1, U5.44 (BOOT0)
BOOT1: R60.2, U5.20 (PB2)
CAN_LED: R15.1, U5.40 (PB4)
CAN_N: J1.2, R46.1, U1.6 (CANL)
CAN_P: J1.3, R46.2, U1.7 (CANH)
CAN_RX: U1.4 (RXD), U5.45 (PB8)
CAN_TX: U1.1 (TXD), U5.46 (PB9)
DB_LED: R14.1, U5.29 (PA8)
FL_CS: R48.2, U5.18 (PB0), U6.1 (~CS)
GND: C1.2, C2.2, C3.2, C4.2, C5.1, C6.2, C7.2, C8.2, C9.1, C10.2, C11.2, C12.2, C13.2, C14.2, C15.2, C16.2, C17.2, C18.2, C20.1, C21.1, C23.2, C28.1, C29.2, C33.2, C34.1, C35.2, C39.2, C41.2, C43.1, C44.2, C45.1, C46.2, C48.1, C49.2, C50.2, C51.2, C52.2, D1.1 (K), D2.1 (K), D3.1 (K), D4.1 (K), D5.2 (A), D6.2 (A), D7.3 (VSS), D13.1 (A1), D13.4 (A3), D18.1 (A1), D18.4 (A3), J1.1, J2.1 (GND), J3.A1 (GND), J3.A12 (GND), J3.B1 (GND), J3.B12 (GND), J3.S1 (SHIELD), J4.4, J5.4, Q1.2 (S), Q2.2 (S), Q3.2 (S), Q5.2 (S), R5.1, R9.2, R10.2, R12.1, R19.1, R20.1, R27.2, R32.1, R35.1, R39.1, R42.1, R43.1, R52.1, R54.1, R60.1, SW1.1, TH1.2, TP3.1, TP5.1, U1.2 (GND), U2.1 (ADJ), U3.2 (GND), U3.5 (ST), U4.2 (GND), U4.5 (ST), U5.8 (VSSA), U5.23 (VSS), U5.35 (VSS), U5.47 (VSS), U6.4 (GND), U8.3 (GND), U8.12 (GND), U8.21 (GND), U9.2 (AGND), U9.9 (AIN3N), U9.10 (AIN3P), U9.19 (DGND), U10.2 (GND), U10.5 (ST), Y1.2, Y1.4
HALL_SCL1: J4.3, R18.2, U5.42 (PB6)
HALL_SCL2: J5.3, R45.2, U5.21 (PB10)
HALL_SDA1: J4.2, R17.1, U5.43 (PB7)
HALL_SDA2: J5.2, R21.1, U5.22 (PB11)
unnamed: D1.2 (A), R1.2
unnamed: D2.2 (A), R2.1
unnamed: D3.2 (A), R3.1
unnamed: D4.2 (A), R16.2
unnamed: D5.1 (K), R14.2
unnamed: D6.1 (K), R15.2
unnamed: D11.2 (A), R30.1
unnamed: D12.2 (A), R31.1
unnamed: D13.6 (K3A4), R33.2, R34.2
unnamed: D13.3 (K1A2), R37.2, R38.2
unnamed: D18.6 (K3A4), R24.1, R29.1
unnamed: D18.3 (K1A2), R28.1, R40.1
unnamed: J3.A5 (CC1), R9.1
unnamed: J3.B5 (CC2), R10.1
unnamed: J6.2, R32.2, R33.1
unnamed: J8.2, R35.2, R37.1
unnamed: Q1.1 (G), R36.1, R39.2
unnamed: Q2.1 (G), R41.1, R42.2
unnamed: Q3.3 (D), R22.1
unnamed: Q3.1 (G), R43.2, R44.2
unnamed: Q5.3 (D), R50.1
unnamed: Q5.1 (G), R52.2, R53.2
unnamed: R8.1, U6.3 (IO2)
unnamed: C20.2, R11.1, R12.2, U8.8 (VBUS)
unnamed: R13.1, U8.9 (~RST)
unnamed: C26.1, R19.2, U9.4 (AIN0N)
unnamed: C27.1, R20.2, U9.5 (AIN1N)
unnamed: C29.1, U9.18 (CAP)
unnamed: C35.1, FB1.2, U11.3 (D)
unnamed: R22.2, R23.1, U11.1 (G)
unnamed: R50.2, R51.1, U12.1 (G)
OSC_IN: C10.1, U5.5 (PD0), Y1.1
OSC_OUT: C11.1, U5.6 (PD1), Y1.3
RESET_FL: R7.1, U5.25 (PB12), U6.7 (IO3)
RGB_DATA: D7.4 (DIN), U5.41 (PB5)
SOL1_RET: D12.1 (K), D16.2 (A), J10.2, Q1.3 (D)
SOL2_RET: D11.1 (K), D15.2 (A), J9.2, Q2.3 (D)
SPI_MISO: U5.16 (PA6), U6.2 (DO(IO1)), U9.15 (DOUT)
SPI_MOSI: U5.17 (PA7), U6.5 (DI(IO0)), U9.16 (DIN)
SPI_SCLK: U5.15 (PA5), U6.6 (CLK), U9.14 (SCLK)
STM_RESET: C8.1, R6.1, SW1.2, U5.7 (NRST)
SWCLK: J2.4 (SWCLK), U5.37 (PA14)
SWDIO: J2.3 (SWDIO), U5.34 (PA13)
TEMP_SENSE: C34.2, R25.1, TH1.1, U5.14 (PA4)
USART_RX: U5.31 (PA10), U8.18 (TXD)
USART_TX: U5.30 (PA9), U8.17 (RXD)
USB_N: J3.A7 (D-), J3.B7 (D-), U8.5 (D-)
USB_P: J3.A6 (D+), J3.B6 (D+), U8.4 (D+)
VALVE1_CTRL: R36.2, U5.26 (PB13)
VALVE2_CTRL: R41.2, U5.27 (PB14)
VPT: C2.1, C18.1, FB1.1, J6.1, J8.1
VPT-SW: R44.1, U5.12 (PA2)
VSOL-SW: R53.1, U5.32 (PA11)
VSOL_SENSE: R47.2, R54.2, TP7.1, U5.19 (PB1)
V_SWD: C44.1, J2.2 (3V3), TP9.1, U10.1 (VIN)
